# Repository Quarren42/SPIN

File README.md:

# SPIN

An open source 12 key, 3 encoder, hotswappable USB-C Macro Pad powered by [QMK Firmware](https://github.com/qmk/qmk_firmware)

You can purchase one at [DMQ Design](http://dmqdesign.com/), or follow the files here and build your own from scratch!

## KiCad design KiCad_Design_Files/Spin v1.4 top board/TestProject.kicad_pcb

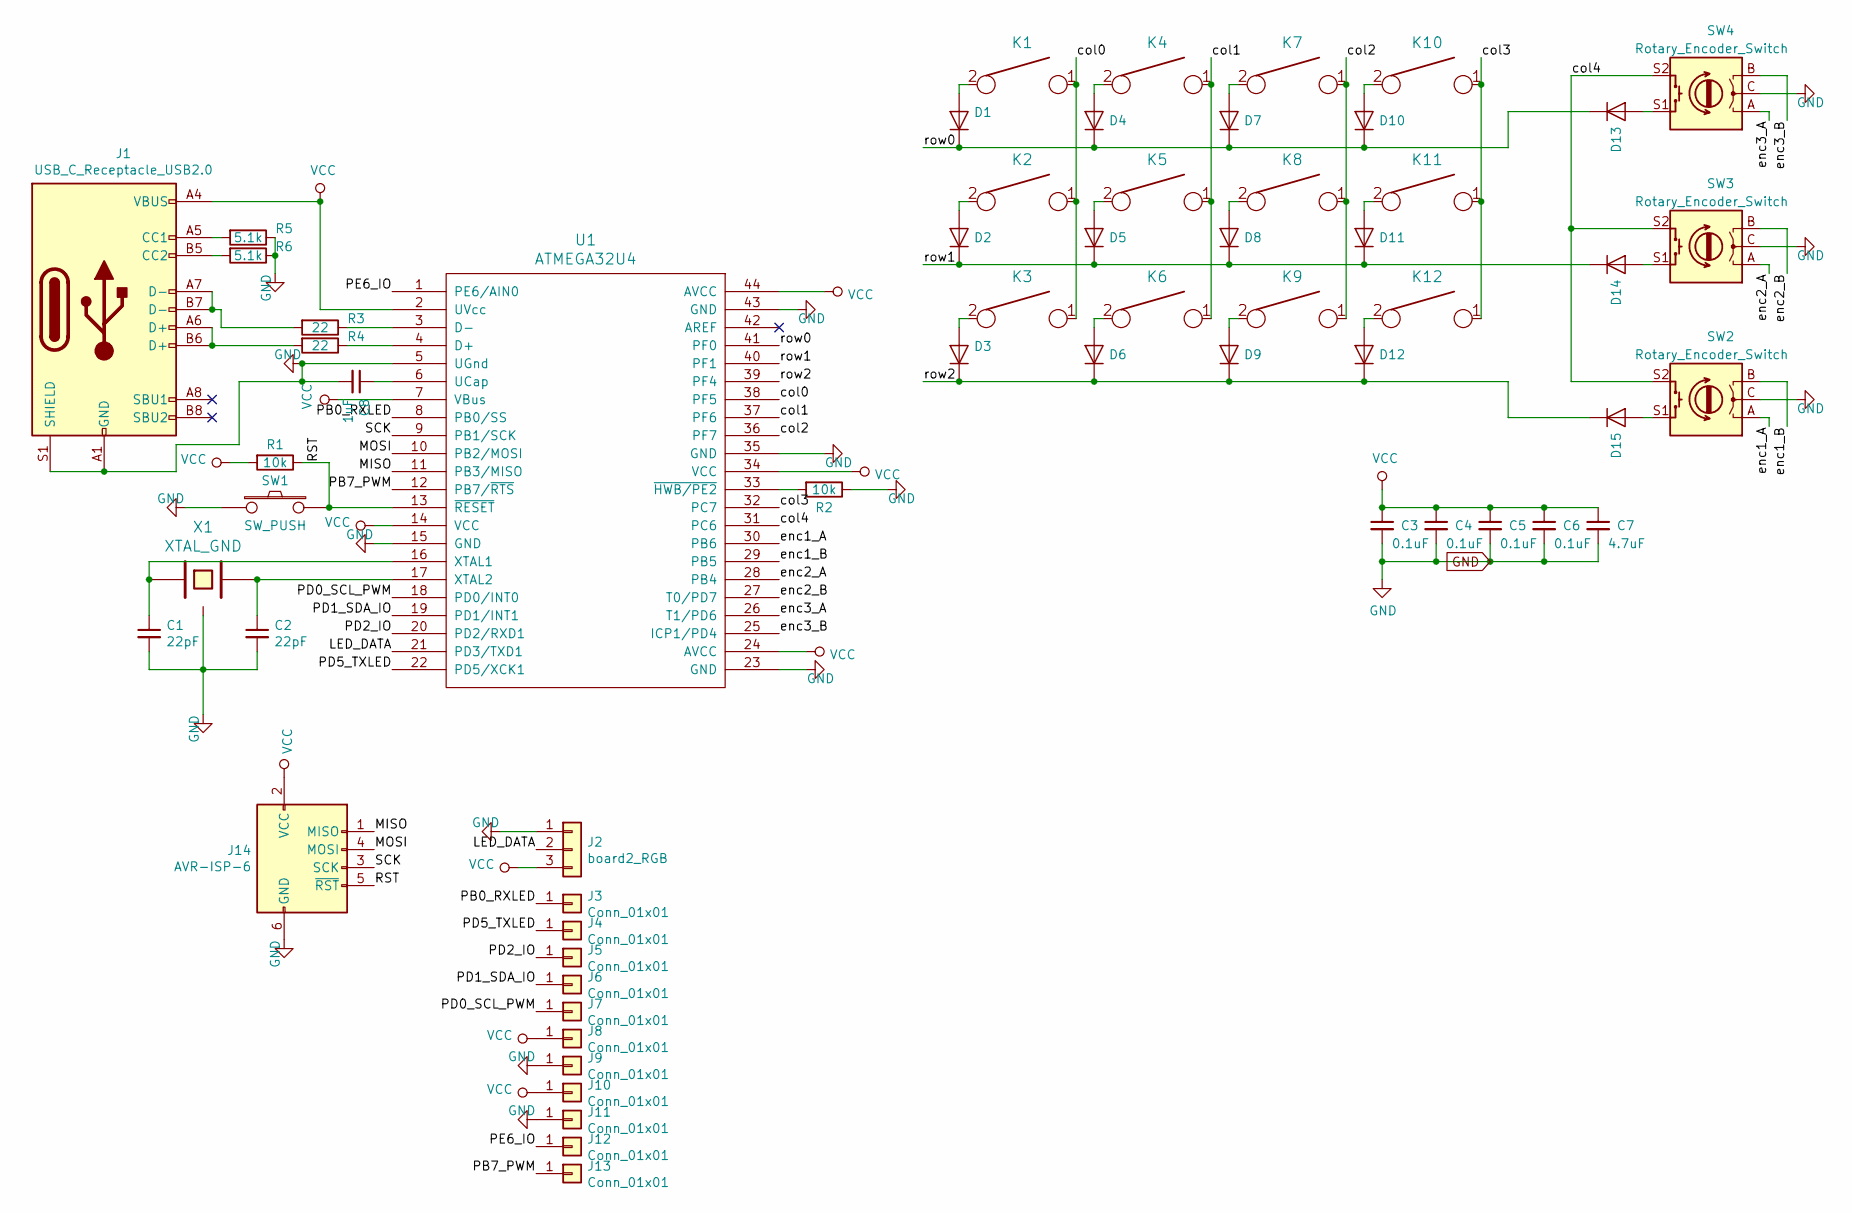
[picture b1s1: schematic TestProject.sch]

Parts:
C1, C2: 22pF; C_0805_2012Metric_Pad1.15x1.40mm_HandSolder
C3, C4, C5, C6: 0.1uF; C_0805_2012Metric_Pad1.15x1.40mm_HandSolder
C7: 4.7uF; C_0805_2012Metric_Pad1.15x1.40mm_HandSolder
C8: 1uF; C_0805_2012Metric_Pad1.15x1.40mm_HandSolder
D1, D2, D3, D4, D5, D6, D7, D8, D9, D10, D11, D12, D13, D14, D15: D; D_SOD123_hand
J1: USB_C_Receptacle_USB2.0; USB_C_Receptacle_Palconn_UTC16-G
J2: board2_RGB; PinHeader_1x03_P2.54mm_Vertical
J3, J4, J5, J6, J7, J8, J9, J10, J11, J12, J13: Conn_01x01; PinSocket_1x01_P2.54mm_Vertical_modified
J14: AVR-ISP-6; PinHeader_2x03_P2.54mm_Vertical_SMD
K1, K2, K3, K4, K5, K6, K7, K8, K9, K10, K11, K12: KEYSW; Kailh_socket_optional
R1, R2: 10k; C_0805_2012Metric_Pad1.15x1.40mm_HandSolder
R3, R4: 22; C_0805_2012Metric_Pad1.15x1.40mm_HandSolder
R5, R6: 5.1k; C_0805_2012Metric_Pad1.15x1.40mm_HandSolder
SW1: SW_PUSH; SW_SPST_EVQP7C
SW2, SW3, SW4: Rotary_Encoder_Switch; RotaryEncoder_Bourns_PEC12R_Horizontal_12mm
U1: ATMEGA32U4; TQFP-44_10x10mm_P0.8mm
X1: XTAL_GND; Crystal_SMD_SeikoEpson_FA238-4Pin_3.2x2.5_mm_fixed

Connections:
/LED_DATA: J2.2, U1.21 (PD3/TXD1)
/MISO: J14.1 (MISO), U1.11 (PB3/MISO)
/MOSI: J14.4 (MOSI), U1.10 (PB2/MOSI)
/PB0_RXLED: J3.1, U1.8 (PB0/SS)
/PB7_PWM: J13.1, U1.12 (PB7/~RTS)
/PD0_SCL_PWM: J7.1, U1.18 (PD0/INT0)
/PD1_SDA_IO: J6.1, U1.19 (PD1/INT1)
/PD2_IO: J5.1, U1.20 (PD2/RXD1)
/PD5_TXLED: J4.1, U1.22 (PD5/XCK1)
/PE6_IO: J12.1, U1.1 (PE6/AIN0)
/RST: J14.5 (~RST), R1.1, SW1.2, U1.13 (~RESET)
/SCK: J14.3 (SCK), U1.9 (PB1/SCK)
/col0: K1.1, K2.1, K3.1, U1.38 (PF5)
/col1: K4.1, K5.1, K6.1, U1.37 (PF6)
/col2: K7.1, K8.1, K9.1, U1.36 (PF7)
/col3: K10.1, K11.1, K12.1, U1.32 (PC7)
/col4: SW2.S2, SW3.S2, SW4.S2, U1.31 (PC6)
/enc1_A: SW2.A, U1.30 (PB6)
/enc1_B: SW2.B, U1.29 (PB5)
/enc2_A: SW3.A, U1.28 (PB4)
/enc2_B: SW3.B, U1.27 (T0/PD7)
/enc3_A: SW4.A, U1.26 (T1/PD6)
/enc3_B: SW4.B, U1.25 (ICP1/PD4)
/row0: D1.1 (K), D4.1 (K), D7.1 (K), D10.1 (K), D13.1 (K), U1.41 (PF0)
/row1: D2.1 (K), D5.1 (K), D8.1 (K), D11.1 (K), D14.1 (K), U1.40 (PF1)
/row2: D3.1 (K), D6.1 (K), D9.1 (K), D12.1 (K), D15.1 (K), U1.39 (PF4)
GND: C1.2, C2.2, C3.2, C4.2, C5.2, C6.2, C7.2, C8.2, J1.A1 (GND), J1.A12 (GND), J1.B1 (GND), J1.B12 (GND), J1.S1 (SHIELD), J2.1, J9.1, J11.1, J14.6 (GND), R2.1, R5.1, R6.1, SW1.1, SW2.C, SW3.C, SW4.C, U1.5 (UGnd), U1.15 (GND), U1.23 (GND), U1.35 (GND), U1.43 (GND), X1.3; also elsewhere on the board
unnamed: C1.1, U1.16 (XTAL1), X1.1
unnamed: C2.1, U1.17 (XTAL2), X1.2
unnamed: C8.1, U1.6 (UCap)
unnamed: D1.2 (A), K1.2
unnamed: D2.2 (A), K2.2
unnamed: D3.2 (A), K3.2
unnamed: D4.2 (A), K4.2
unnamed: D5.2 (A), K5.2
unnamed: D6.2 (A), K6.2
unnamed: D7.2 (A), K7.2
unnamed: D8.2 (A), K8.2
unnamed: D9.2 (A), K9.2
unnamed: D10.2 (A), K10.2
unnamed: D11.2 (A), K11.2
unnamed: D12.2 (A), K12.2
unnamed: D13.2 (A), SW4.S1
unnamed: D14.2 (A), SW3.S1
unnamed: D15.2 (A), SW2.S1
unnamed: J1.A5 (CC1), R5.2
unnamed: J1.A6 (D+), J1.B6 (D+), R4.2
unnamed: J1.A7 (D-), J1.B7 (D-), R3.2
unnamed: J1.B5 (CC2), R6.2
unnamed: R2.2, U1.33 (~HWB/PE2)
unnamed: R3.1, U1.3 (D-)
unnamed: R4.1, U1.4 (D+)
VCC: C3.1, C4.1, C5.1, C6.1, C7.1, J1.A4 (VBUS), J1.A9 (VBUS), J1.B4 (VBUS), J1.B9 (VBUS), J2.3, J8.1, J10.1, J14.2 (VCC), R1.2, U1.2 (UVcc), U1.7 (VBus), U1.14 (VCC), U1.24 (AVCC), U1.34 (VCC), U1.44 (AVCC); also elsewhere on the board

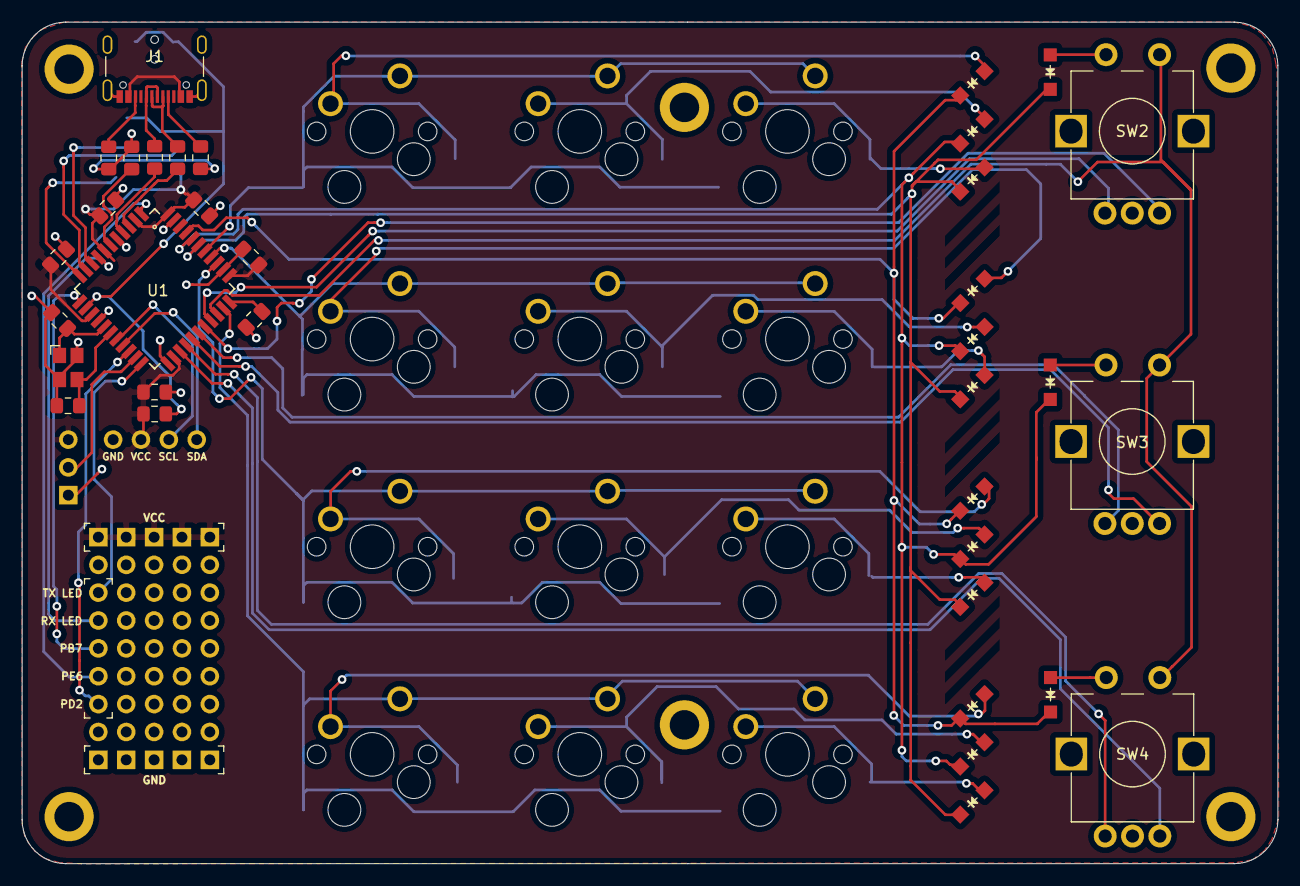
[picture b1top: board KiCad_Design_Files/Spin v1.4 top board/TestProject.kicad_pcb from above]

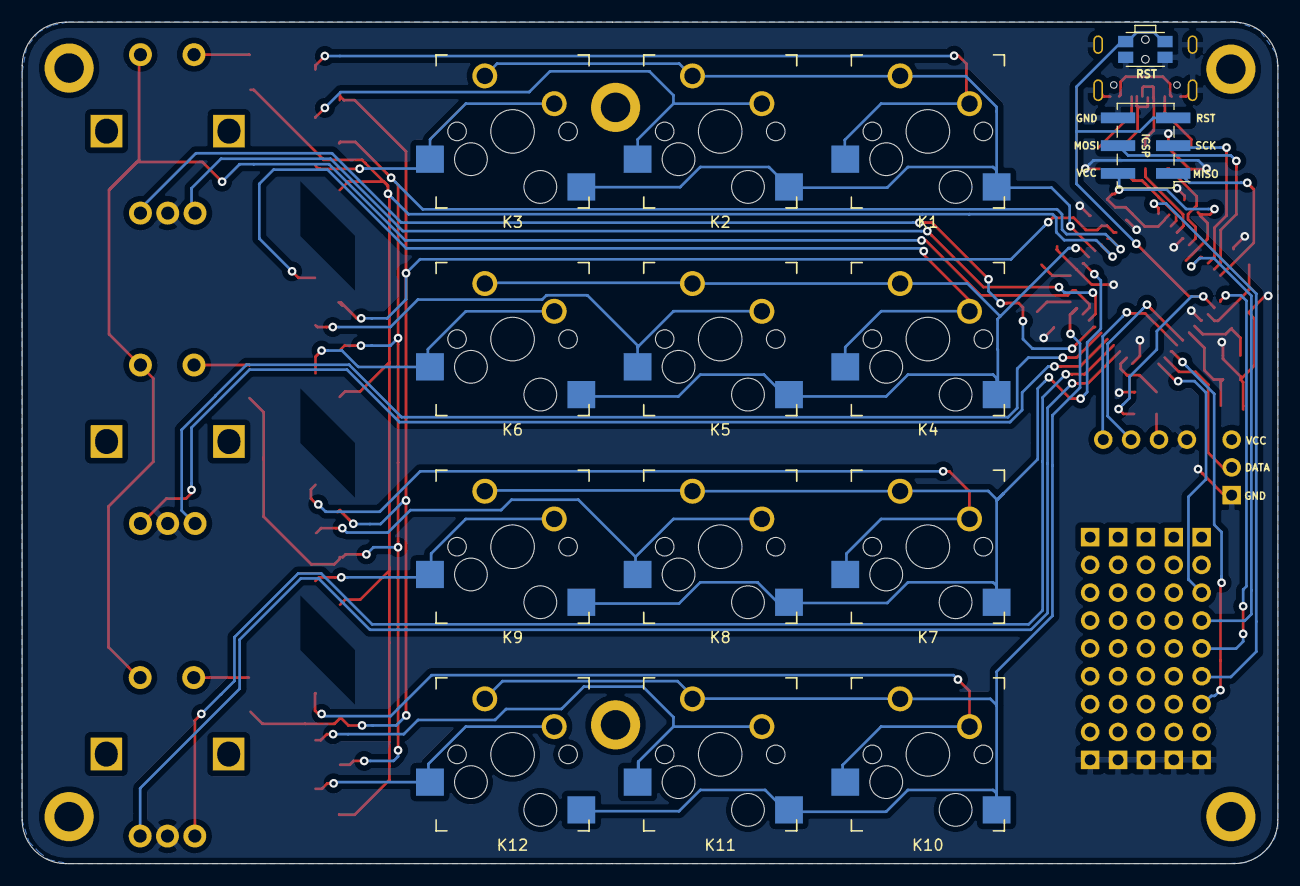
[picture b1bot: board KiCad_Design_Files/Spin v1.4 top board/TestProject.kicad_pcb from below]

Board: 2 copper layers, 114.9 x 77.0 mm, 69 parts (2 on the bottom side), 53 nets.

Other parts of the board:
J10#2, J10#3, J10#4, J10#5, J11#2, J11#3, J11#4, J11#5: Conn_01x01; PinSocket_1x01_P2.54mm_Vertical_modified

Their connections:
GND: J11#2.1, J11#3.1, J11#4.1, J11#5.1; also elsewhere on the board
VCC: J10#2.1, J10#3.1, J10#4.1, J10#5.1; also elsewhere on the board

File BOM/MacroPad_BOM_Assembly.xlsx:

Ref. Designator | Manufacturer Part Number | Qty | Description | Package
J1 | USB4105-GF-A | 1 | USB-C USB 2.0 Receptacle Connector 24 (16 + 8 dummy) position SMD
C3, C4, C5, C6 | CL21B104KACNNNC | 4 | Ceramic Cap, 0805, 0.1uF | 0805
R3, R4 | RC0805JR-0722RL | 2 | Resistor, 0805, 22Ω | 0805
R1, R2 | RNCP0805FTD10K0 | 2 | Resistor, 0805, 10kΩ | 0805
C1, C2 | C0805C220J5GACTU | 2 | Ceramic Cap, 0805, 22pF | 0805
X1 | FA-238 16.0000MB-K3 | 1 | CRYSTAL 16.00 MHZ 10PF SMD | 4-SMD, No Lead
U1 | ATMEGA32U4-AU | 1 | IC MCU 8BIT 32KB FLASH 44TQFP | 44-TQFP
SW1 | EVQ-P7C01P | 1 | SWITCH TACTILE SPST-NO 0.05A 12V
D1, D2, D3, D4, D5, D6, D7, D8, D9, D10, D11, D12, D13, D14, D15 | 1N4148W-HE3-08 | 15 | DIODE GEN PURP 75V 150MA SOD123 | SOD123
C7 | CL21F475ZPFNNNE | 1 | Ceramic Cap, 0805, 4.7uF | 0805
C8 | CC0805ZRY5V8BB105 | 1 | Ceramic cap, 0805, 1uF | 0805
R5, R6 | CRG0805F1K5 | 2 | Resistor, 0805, 1.5kΩ | 0805
D101, D102, D103 | WS2812B | 3 | WS2812B RGB LED | PLCC4
R101 | CRGCQ0805F330R | 1 | Resistor, 0805, 330Ω | 0805

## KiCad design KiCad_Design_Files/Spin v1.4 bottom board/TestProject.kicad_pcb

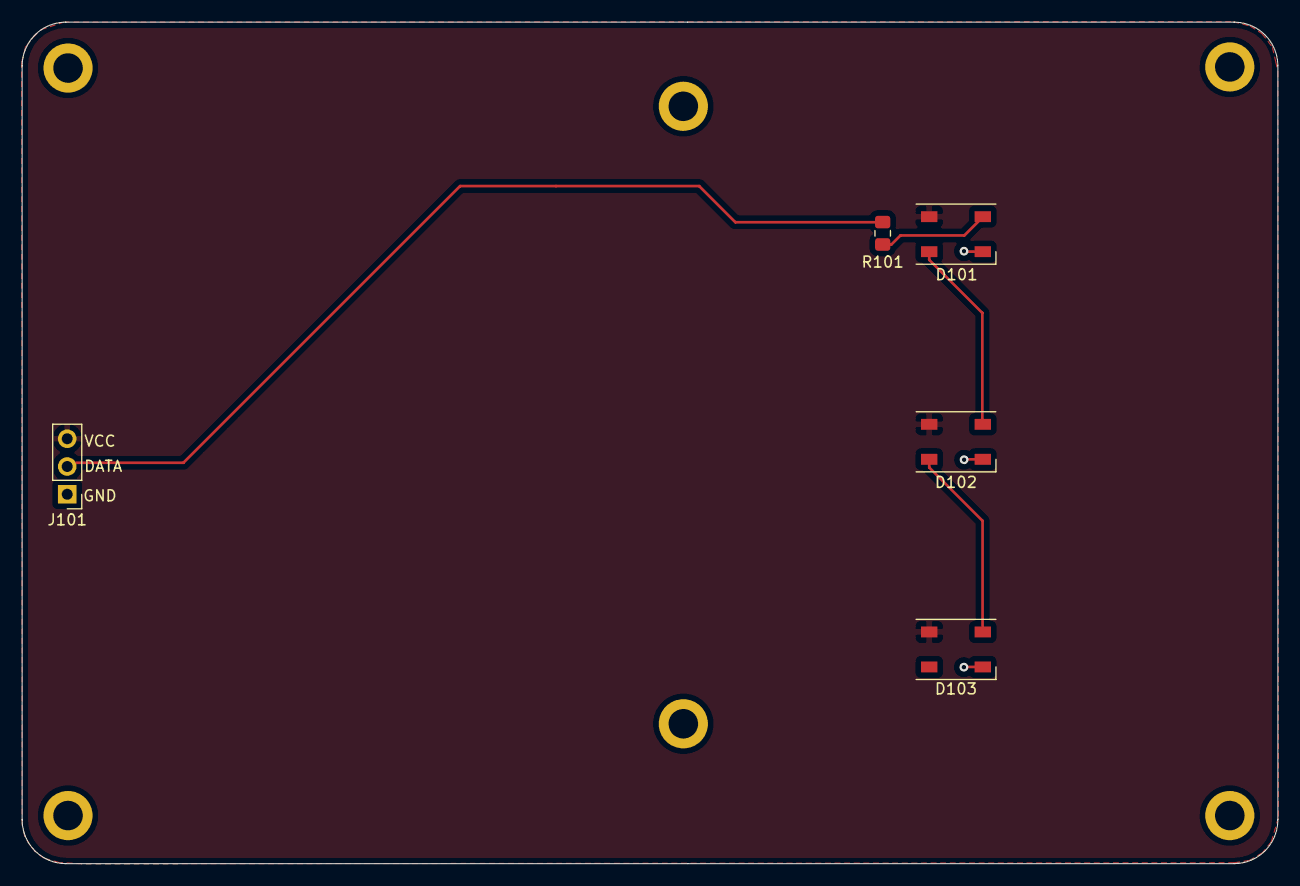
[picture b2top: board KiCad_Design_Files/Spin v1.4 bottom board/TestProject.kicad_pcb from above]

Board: 2 copper layers, 114.9 x 77.0 mm, 5 parts (0 on the bottom side), 6 nets.

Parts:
D101, D102, D103: WS2812B; LED_WS2812B_PLCC4_5.0x5.0mm_P3.2mm
J101: board2_RGB; PinHeader_1x03_P2.54mm_Vertical
R101: 330; C_0805_2012Metric_Pad1.15x1.40mm_HandSolder

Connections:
/LED_DATA: J101.2, R101.2
GND: D101.3, D102.3, D103.3, J101.1
unnamed: D101.2, D102.4
unnamed: D101.4, R101.1
unnamed: D102.2, D103.4
VCC: D101.1, D102.1, D103.1, J101.3

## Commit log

2020-04-11 Created LICENSE file
    Added the Creative Commons Attribution Share Alike 4.0 International license.
2020-04-12 Updated readme
    Updated readme with link to QMK firmware
2020-04-12 added image for the SPIN
2020-04-12 added website
    Added link to DMQdesign.com
2020-04-12 make text link to site
    made DMQdesign link to the actual site
2020-04-14 updated readme with new pic
2020-04-15 Added Gerbers for top/btm
    Added zipped gerber files for top and bottom board. Need to double check licenses for the part libs I used before sharing.
2020-04-21 added 3D CAD, KiCad Files, KiCad Libraries, and BOM
2021-03-03 Added interactive BOM
    Added interactive BOM html file, should give some clarification on component placement compared to digging through the gerbers.
2024-07-30 Added production files from SPIN production run
    Added production files from SPIN production run - full BOM for JLCPCB assembly with JLCPCB part numbers, centroid/pos file, and top/bottom board panelized with mousebites.
